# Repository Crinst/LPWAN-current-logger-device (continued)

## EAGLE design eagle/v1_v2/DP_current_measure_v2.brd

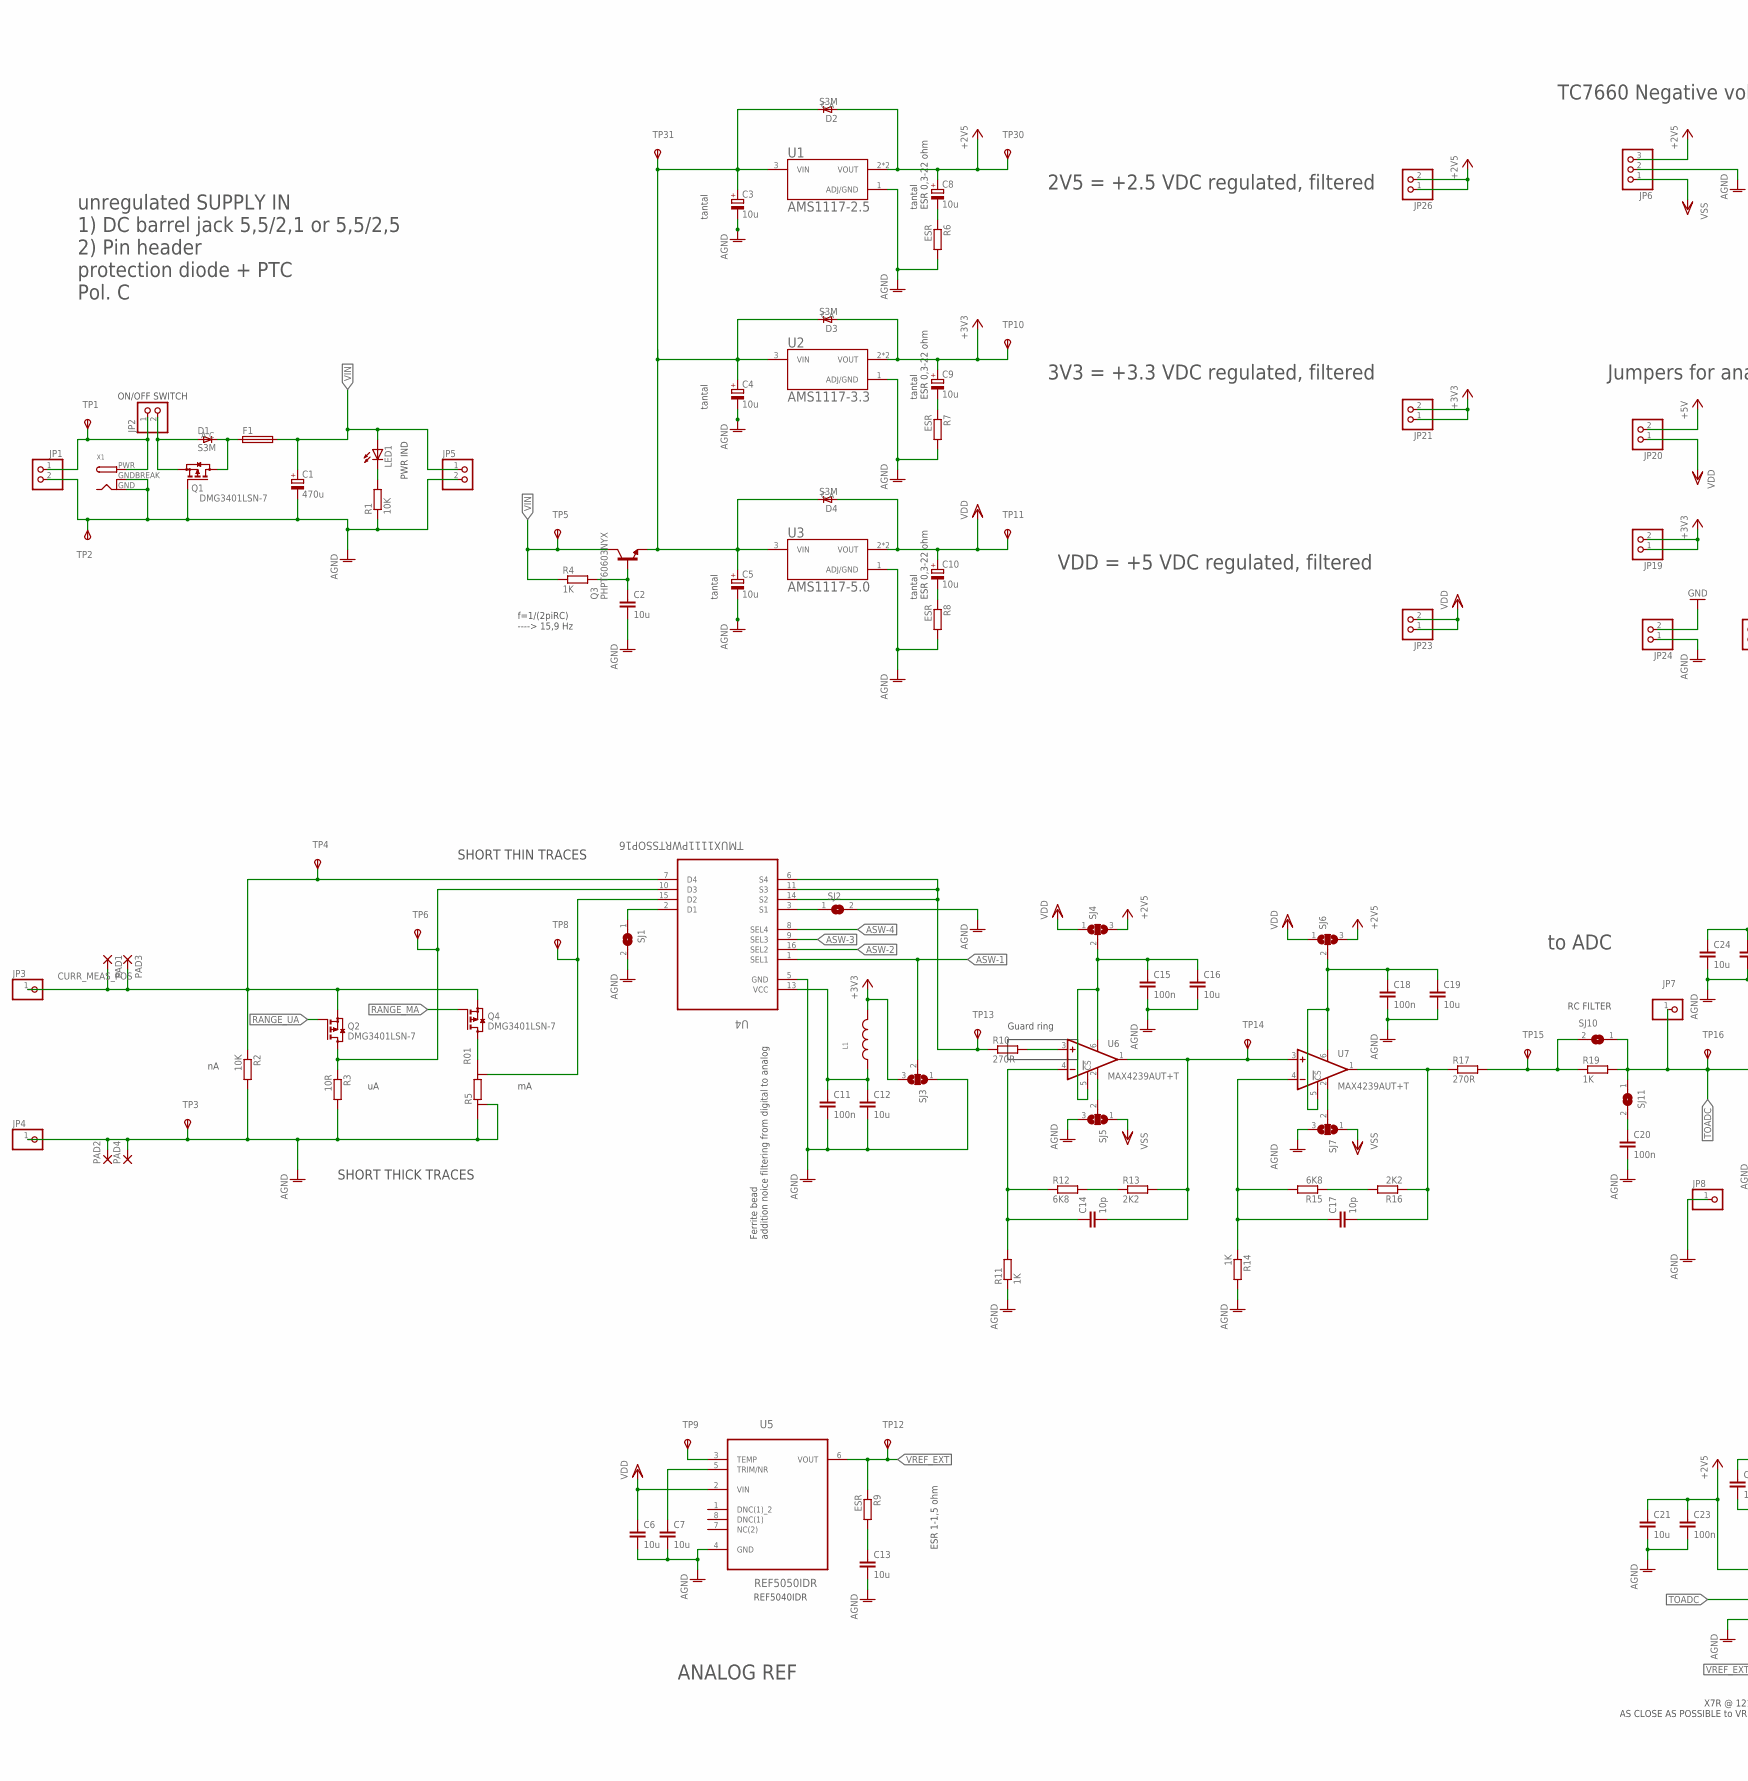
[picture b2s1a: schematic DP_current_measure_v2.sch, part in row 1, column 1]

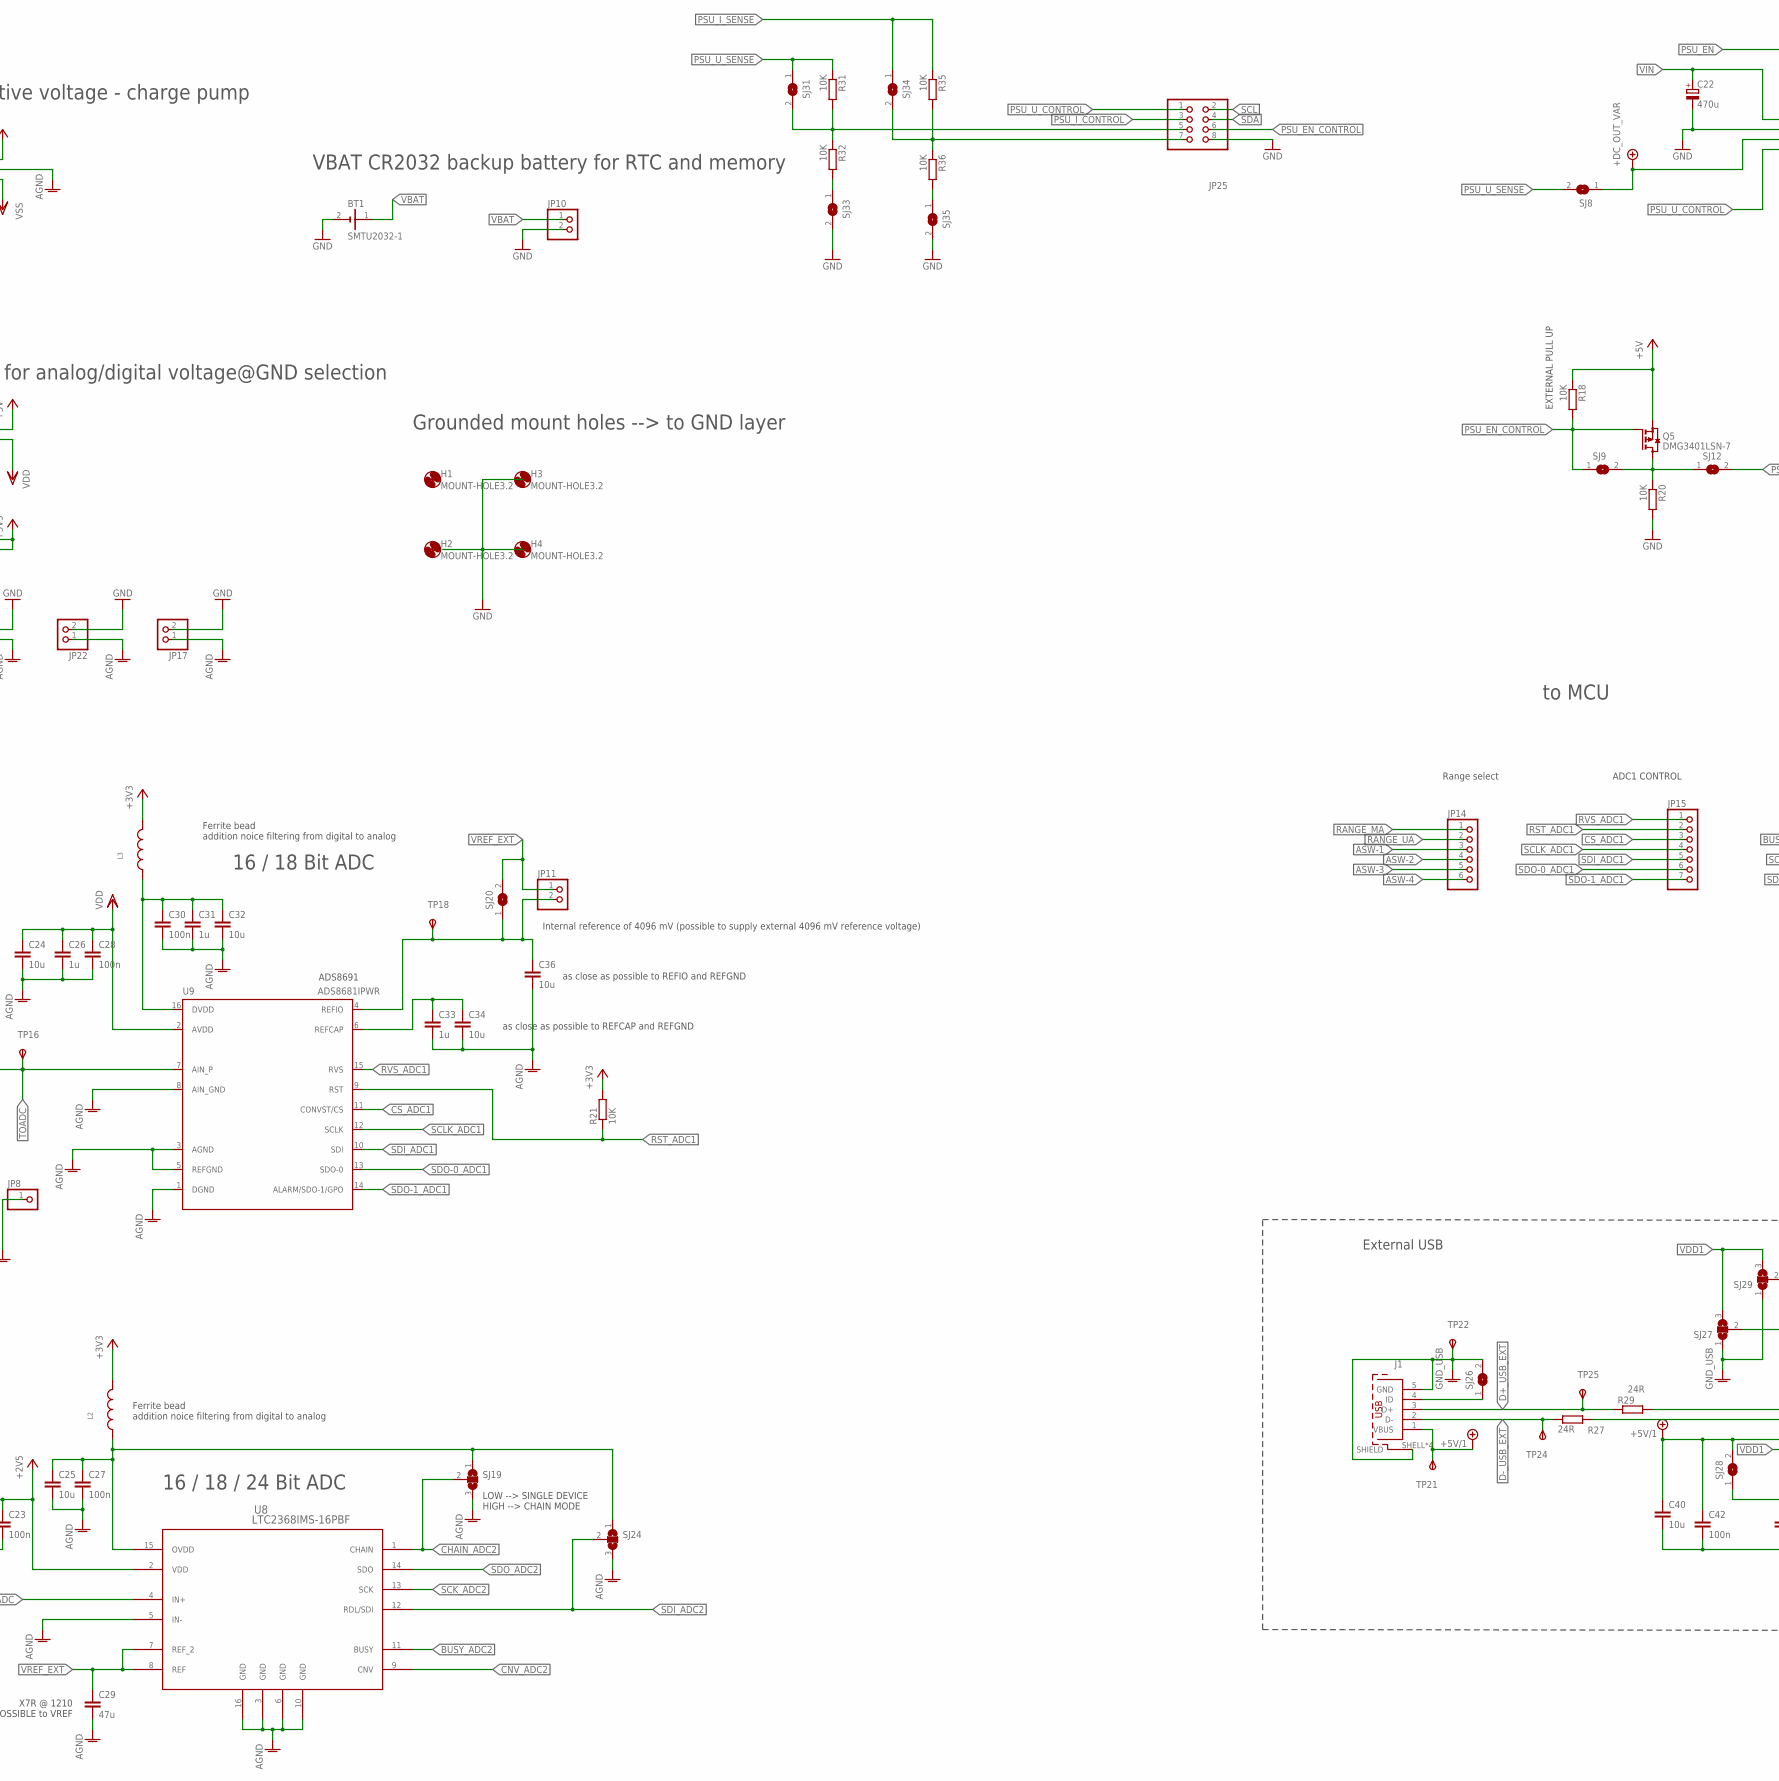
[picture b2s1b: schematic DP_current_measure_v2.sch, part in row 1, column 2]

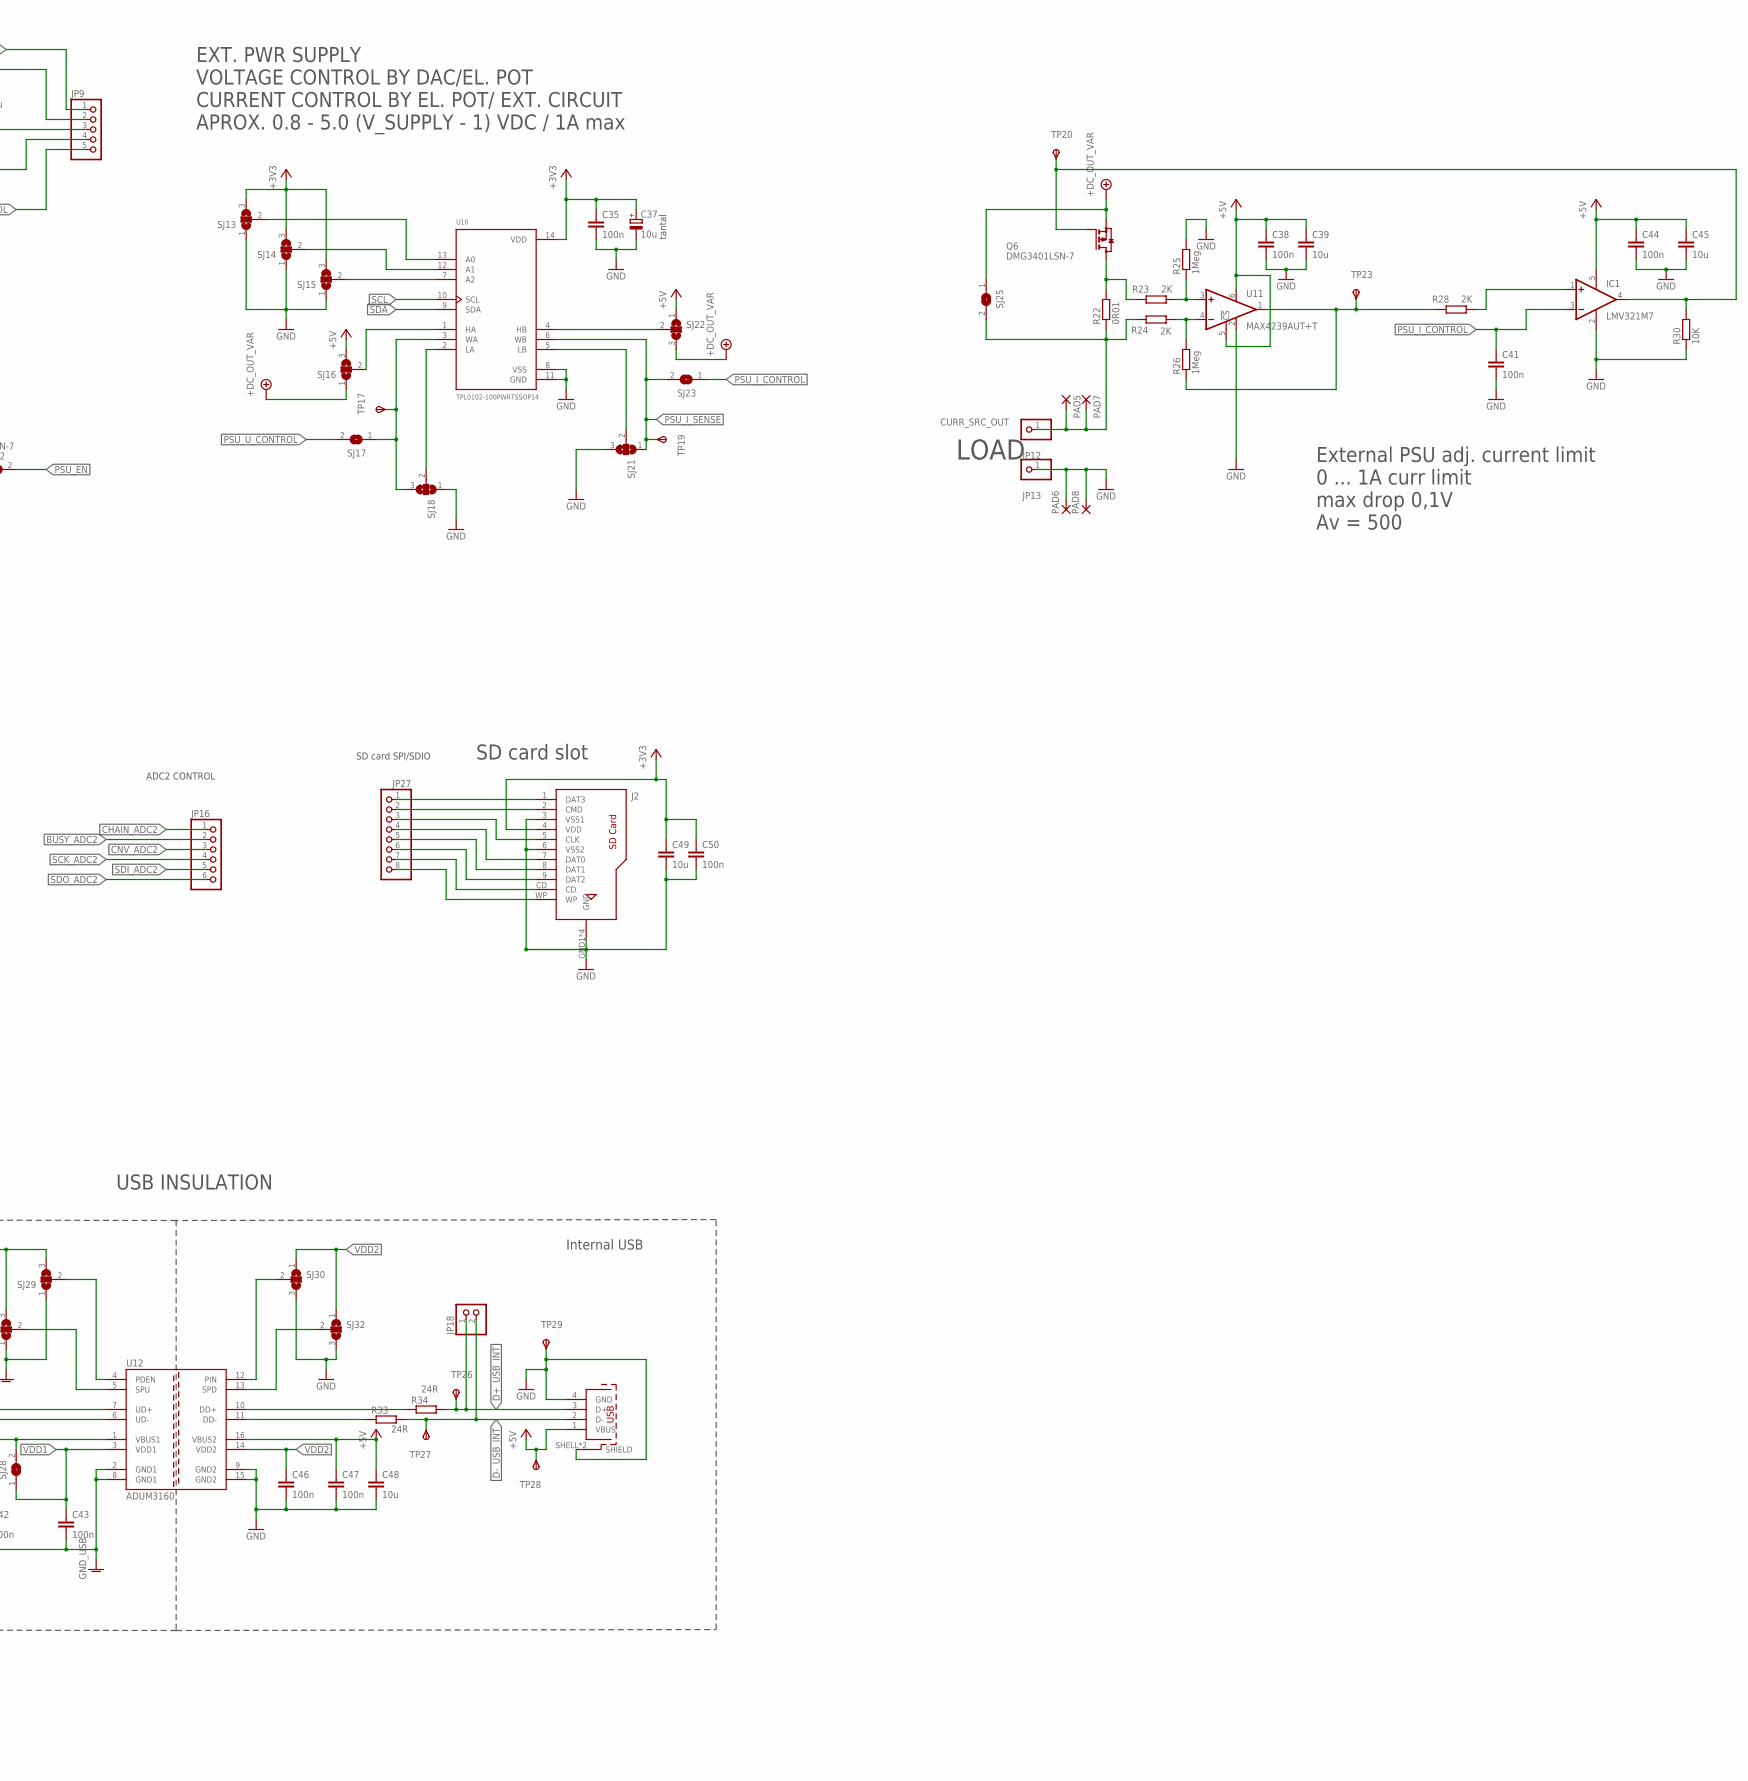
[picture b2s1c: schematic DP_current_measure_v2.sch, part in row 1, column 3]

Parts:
BT1: SMTU2032-1; RENATA_SMTU2032-1
C1, C22: 470u; PANASONIC_G
C2, C6, C7, C12, C13, C16, C19, C21, C24, C25, C32, C34, C36, C39, C40, C45, C48, C49: 10u; C1206
C3, C4, C5, C8, C9, C10, C37: 10u; SMC_B
C11, C15, C18, C23, C27, C28, C30, C35, C38, C41, C42, C43, C44, C46, C47, C50: 100n; C0805
C14, C17: 10p; C0805
C20: 100n; C1206
C26, C31, C33: 1u; C0805
C29: 47u; C1210
D1, D2, D3, D4: S3M; DO214AC
F1: MF-MSMF050-2; 1812
H1, H2, H3, H4: MOUNT-HOLE3.2; 3,2
IC1: LMV321M7; SC70-5L
J1: 629105150521
J2: 693063020911
J3: 614004185023
JP1, JP2, JP5, JP10, JP11, JP17, JP18, JP19, JP20, JP21, JP22, JP23, JP24, JP26: PINHD-1X2; 1X02
JP3, JP4, JP7, JP8, JP12, JP13: PINHD-1X1; 1X01
JP6: PINHD-1X3; 1X03
JP9: PSU_STEP_DOWN; 1X05
JP14, JP16: PINHD-1X6; 1X06
JP15: PINHD-1X7; 1X07
JP25: PINHD-2X4; 2X04
JP27: PINHD-1X8; 1X08
L1, L2, L3: WE-CBF_0805_742792036_WB_HS; WE-CBF_0805(W=3.0)
LED1: LEDCHIPLED_0805; CHIPLED_0805
PAD1, PAD2, PAD3, PAD4, PAD5, PAD6, PAD7, PAD8: WIREPADSMD2,54-5,08; SMD2,54-5,08
Q1, Q2, Q4, Q5, Q6: DMG3401LSN-7; SOT23
Q3: PHPT60603NYX; TO127P600X120-5N
R1, R2, R18, R20, R21, R30, R31, R32, R35, R36: 10K; R0805
R3: 10R; R0805
R4, R11, R14, R19: 1K; R0805
R5: R01; R2512
R6, R7, R8, R9: ESR; R0805
R10, R17: 270R; R0805
R12, R15: 6K8; R0805
R13, R16: 2K2; R0805
R22: 0R01; R0805
R23, R24, R28: 2K; R0805
R25, R26: 1Meg; R0805
R27, R29, R33, R34: 24R; R0805
SJ1, SJ2, SJ8, SJ9, SJ10, SJ11, SJ12, SJ17, SJ20, SJ23, SJ25, SJ26, SJ28, SJ31, SJ33, SJ34, SJ35: SJ
SJ3, SJ4, SJ5, SJ6, SJ7, SJ13, SJ14, SJ15, SJ16, SJ18, SJ19, SJ21, SJ22, SJ24, SJ27, SJ29, SJ30, SJ32: SJ2W; SJ_2
TP1, TP2, TP3, TP4, TP5, TP6, TP8, TP9, TP10, TP11, TP12, TP13, TP14, TP15, TP16, TP17, TP18, TP19, TP20, TP21, TP22, TP23, TP24, TP25, TP26, TP27, TP28, TP29, TP30, TP31: TPSB1,27; B1,27
U1: AMS1117-2.5; SOT229P700X180-4N
U2: AMS1117-3.3; SOT229P700X180-4N
U3: AMS1117-5.0; SOT229P700X180-4N
U4: TMUX1111PWRTSSOP16; SOP65P640X110-16N
U5: REF5050IDR; SOIC127P600X175-8N
U6, U7, U11: MAX4239AUT+T; SOT23-6
U8: LTC2368IMS-16PBF; MSOP-16_MS
U9: ADS8681IPWR; SOP65P640X120-16N
U10: TPL0102-100PWRTSSOP14; SOP65P640X120-14N
U12: ADUM3160; SO16W
X1: DCBARRELPTH; DCJACK_2MM_PTH

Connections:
+2V5: C8.+, C21.1, C23.1, D2.A, JP6.3, JP26.1, JP26.2, SJ4.3, SJ6.3, TP30.TP, U1.2 (VOUT), U1.4 (VOUT), U8.2 (VDD)
+3V3: C9.+, C35.1, C37.+, C49.1, C50.1, D3.A, J2.4 (VDD), JP19.1, JP19.2, JP21.1, JP21.2, L1.2, L2.2, L3.2, R21.2, SJ3.3, SJ13.3, SJ14.3, SJ15.3, TP10.TP, U2.2 (VOUT), U2.4 (VOUT), U10.14 (VDD)
+5V: C38.1, C39.1, C44.1, C45.1, C47.1, C48.1, IC1.5 (V+), J3.1 (VBUS), JP20.2, Q5.2 (S), R18.1, SJ16.3, SJ22.1, TP28.TP, U11.5 (!CS), U11.6 (V+), U12.16 (VBUS2)
+5V/1: C40.1, C42.1, J1.1 (VBUS), SJ28.2, TP21.TP, U12.1 (VBUS1)
AGND: C1.-, C2.2, C3.-, C4.-, C5.-, C6.2, C7.2, C11.2, C12.2, C13.2, C15.2, C16.2, C18.2, C19.2, C20.2, C21.2, C23.2, C24.2, C25.2, C26.2, C27.2, C28.2, C29.2, C30.2, C31.2, C32.2, C33.2, C34.2, C36.2, JP1.2, JP4.1, JP5.2, JP6.2, JP8.1, JP17.1, JP22.1, JP24.1, PAD2.1, PAD4.1, Q1.1 (G), R1.1, R2.2, R3.2, R5.E1, R5.I1, R6.2, R7.2, R8.2, R11.1, R14.2, SJ1.2, SJ2.2, SJ3.1, SJ5.3, SJ7.3, SJ19.3, SJ24.3, TP2.TP, TP3.TP, U1.1 (ADJ/GND), U2.1 (ADJ/GND), U3.1 (ADJ/GND), U4.5 (GND), U5.4 (GND), U8.3 (GND), U8.5 (IN-), U8.6 (GND), U8.10 (GND), U8.16 (GND), U9.1 (DGND), U9.3 (AGND), U9.5 (REFGND), U9.8 (AIN_GND), X1.GND, X1.GNDBREAK
ASW-1: JP14.3, SJ3.2, U4.1 (SEL1)
ASW-2: JP14.4, U4.16 (SEL2)
ASW-3: JP14.5, U4.9 (SEL3)
ASW-4: JP14.6, U4.8 (SEL4)
BUSY_ADC2: JP16.2, U8.11 (BUSY)
CHAIN_ADC2: JP16.1, SJ19.2, U8.1 (CHAIN)
CNV_ADC2: JP16.3, U8.9 (CNV)
CS_ADC1: JP15.3, U9.11 (CONVST/CS)
CURR_MEAS_POS: JP3.1, PAD1.1, PAD3.1, Q2.2 (S), Q4.2 (S), R2.1, TP4.TP, U4.7 (D4)
CURR_SRC_OUT: JP12.1, PAD5.1, PAD7.1, R22.1, R24.1, SJ25.2
D+_USB_EXT: J1.3 (D+), R29.1, TP25.TP
D+_USB_INT: J3.3 (D+), JP18.1, R34.2, TP26.TP
D-_USB_EXT: J1.2 (D-), R27.1, TP24.TP
D-_USB_INT: J3.2 (D-), JP18.2, R33.2, TP27.TP
DC_OUT_VAR: JP9.4, Q6.2 (S), SJ8.1, SJ16.1, SJ22.3, SJ25.1
GND: BT1.2 (-), C22.-, C35.2, C37.-, C38.2, C39.2, C41.2, C44.2, C45.2, C46.2, C47.2, C48.2, C49.2, C50.2, IC1.2 (V-), J2.3 (VSS1), J2.6 (VSS2), J2.GND1 (GND), J2.GND2 (GND), J2.GND3 (GND), J2.GND4 (GND), J3.4 (GND), J3.SHELL (SHIELD), J3.SHELL1 (SHIELD), JP9.3, JP10.2, JP13.1, JP17.2, JP22.2, JP24.2, JP25.8, PAD6.1, PAD8.1, R20.2, R25.2, R30.1, SJ13.1, SJ14.1, SJ15.1, SJ18.1, SJ21.3, SJ30.3, SJ32.3, SJ33.2, SJ35.2, TP29.TP, U10.8 (VSS), U10.11 (GND), U11.2 (V-), U12.9 (GND2), U12.15 (GND2)
GND_EXT: C40.2, C42.2, C43.2, J1.5 (GND), J1.SHELL (SHIELD), J1.SHELL1 (SHIELD), J1.SHELL2 (SHIELD), J1.SHELL3 (SHIELD), SJ26.2, SJ27.1, SJ29.1, TP22.TP, U12.2 (GND1), U12.8 (GND1)
MA_RANGE_SENSE: R5.E2, TP8.TP, U4.15 (D2)
unnamed: C17.2, R16.1, R17.1, U7.1 (OUT)
unnamed: R15.1, R16.2
unnamed: C17.1, R14.1, R15.2, U7.4 (-IN)
unnamed: R12.2, R13.1
unnamed: C14.2, R13.2, TP14.TP, U6.1 (OUT), U7.3 (+IN)
unnamed: R10.1, TP13.TP, U4.6 (S4), U4.11 (S3), U4.14 (S2)
unnamed: C14.1, R11.2, R12.1, U6.4 (-IN)
unnamed: C11.1, C12.1, L1.1, U4.13 (VCC)
unnamed: SJ16.2, U10.1 (HA)
unnamed: SJ17.1, SJ18.3, TP17.TP, U10.3 (WA)
unnamed: Q6.3 (D), R22.2, R23.1
unnamed: SJ15.2, U10.7 (A2)
unnamed: SJ7.2, U7.2 (V-)
unnamed: R10.2, U6.3 (+IN)
unnamed: C9.-, R7.1
unnamed: Q4.3 (D), R5.I2
unnamed: SJ5.2, U6.2 (V-)
unnamed: R17.2, R19.1, SJ10.2, TP15.TP
unnamed: C10.-, R8.1
unnamed: SJ13.2, U10.13 (A0)
unnamed: C8.-, R6.1
unnamed: C2.1, Q3.4 (B), R4.2
unnamed: C7.1, U5.5 (TRIM/NR)
unnamed: C20.1, SJ11.2
unnamed: SJ14.2, U10.12 (A1)
unnamed: JP25.7, R35.2, R36.1, SJ34.2
unnamed: JP25.5, R31.2, R32.1, SJ31.2
unnamed: R36.2, SJ35.1
unnamed: R32.2, SJ33.1
unnamed: R26.1, R28.1, TP23.TP, U11.1 (OUT)
unnamed: SJ22.2, U10.4 (HB)
unnamed: J1.4 (ID), SJ26.1
unnamed: R23.2, R25.1, U11.3 (+IN)
unnamed: SJ18.2, U10.2 (LA)
unnamed: IC1.4 (OUT), Q6.1 (G), R30.2, TP20.TP
unnamed: R24.2, R26.2, U11.4 (-IN)
unnamed: C18.1, C19.1, SJ6.2, U7.5 (!CS), U7.6 (V+)
unnamed: D1.C, F1.1, Q1.3 (D)
unnamed: C33.1, C34.1, U9.6 (REFCAP)
unnamed: C36.1, JP11.2, SJ20.1, TP18.TP, U9.4 (REFIO)
unnamed: D1.A, JP2.2, Q1.2 (S)
unnamed: R34.1, U12.10 (DD+)
unnamed: LED1.C, R1.2
unnamed: SJ21.2, U10.5 (LB)
unnamed: C15.1, C16.1, SJ4.2, U6.5 (!CS), U6.6 (V+)
unnamed: TP9.TP, U5.3 (TEMP)
unnamed: J2.1 (DAT3), JP27.1
unnamed: J2.2 (CMD), JP27.2
unnamed: J2.5 (CLK), JP27.3
unnamed: J2.7 (DAT0), JP27.4
unnamed: SJ30.2, U12.12 (PIN)
unnamed: SJ32.2, U12.13 (SPD)
unnamed: SJ27.2, U12.5 (SPU)
unnamed: SJ29.2, U12.4 (PDEN)
unnamed: SJ2.1, U4.3 (S1)
unnamed: SJ1.1, U4.2 (D1)
unnamed: J2.8 (DAT1), JP27.5
unnamed: C13.1, R9.2
unnamed: J2.9 (DAT2), JP27.6
unnamed: J2.CD, JP27.7
unnamed: J2.WP, JP27.8
unnamed: JP1.1, JP2.1, TP1.TP, X1.PWR
unnamed: C30.1, C31.1, C32.1, L3.1, U9.16 (DVDD)
unnamed: C25.1, C27.1, L2.1, SJ19.1, SJ24.1, U8.15 (OVDD)
OPAMP_LEADS: IC1.1 (+IN), R28.2
PSU_EN: JP9.1, SJ12.2
PSU_EN_CONTROL: JP25.6, Q5.1 (G), R18.2, SJ9.1
PSU_EN_LEAD: Q5.3 (D), R20.1, SJ9.2, SJ12.1
PSU_I_CONTROL: C41.1, IC1.3 (-IN), JP25.3, SJ23.1
PSU_I_SENSE: R35.1, SJ21.1, SJ23.2, SJ34.1, TP19.TP, U10.6 (WB)
PSU_U_CONTROL: JP9.5, JP25.1, SJ17.2
PSU_U_SENSE: R31.1, SJ8.2, SJ31.1
RANGE_MA: JP14.1, Q4.1 (G)
RANGE_UA: JP14.2, Q2.1 (G)
RST_ADC1: JP15.2, R21.1, U9.9 (RST)
RVS_ADC1: JP15.1, U9.15 (RVS)
SCK_ADC2: JP16.4, U8.13 (SCK)
SCL: JP25.2, U10.10 (SCL)
SCLK_ADC1: JP15.4, U9.12 (SCLK)
SDA: JP25.4, U10.9 (SDA)
SDI_ADC1: JP15.5, U9.10 (SDI)
SDI_ADC2: JP16.5, SJ24.2, U8.12 (RDL/SDI)
SDO-0_ADC1: JP15.6, U9.13 (SDO-0)
SDO-1_ADC1: JP15.7, U9.14 (ALARM/SDO-1/GPO)
SDO_ADC2: JP16.6, U8.14 (SDO)
TOADC: JP7.1, R19.2, SJ10.1, SJ11.1, TP16.TP, U8.4 (IN+), U9.7 (AIN_P)
UA_RANGE_SENSE: Q2.3 (D), R3.1, TP6.TP, U4.10 (D3)
USB_EXT_N: R27.2, U12.6 (UD-)
USB_EXT_P: R29.2, U12.7 (UD+)
USB_INT_N: R33.1, U12.11 (DD-)
VBAT: BT1.1 (+), JP10.1
VDD: C6.1, C10.+, C24.1, C26.1, C28.1, D4.A, JP20.1, JP23.1, JP23.2, SJ4.1, SJ6.1, TP11.TP, U3.2 (VOUT), U3.4 (VOUT), U5.2 (VIN), U9.2 (AVDD)
VDD1: C43.1, SJ27.3, SJ28.1, SJ29.3, U12.3 (VDD1)
VDD2: C46.1, SJ30.1, SJ32.1, U12.14 (VDD2)
VIN: C1.+, C22.+, F1.2, JP5.1, JP9.2, LED1.A, Q3.5 (C), R4.1, TP5.TP
VREF_EXT: C29.1, JP11.1, R9.1, SJ20.2, TP12.TP, U5.6 (VOUT), U8.7 (REF_2), U8.8 (REF)
VSS: JP6.1, SJ5.1, SJ7.1
V_FILTR_UNREG: C3.+, C4.+, C5.+, D2.C, D3.C, D4.C, Q3.1 (E), Q3.2 (E), Q3.3 (E), TP31.TP, U1.3 (VIN), U2.3 (VIN), U3.3 (VIN)

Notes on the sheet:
SHORT THICK TRACES
SHORT THIN TRACES
unregulated SUPPLY IN 1) DC barrel jack 5,5/2,1 or 5,5/2,5 2) Pin header protection diode + PTC Pol. C
to MCU
to ADC
tantal
tantal ESR 0,3-22 ohm
f=1/(2piRC) ----> 15,9 Hz
VDD = +5 VDC regulated, filtered
as close as possible to REFIO and REFGND
as close as possible to REFCAP and REFGND
ADS8691
3V3 = +3.3 VDC regulated, filtered
REF5040IDR
LOW --> SINGLE DEVICE HIGH --> CHAIN MODE
X7R @ 1210 AS CLOSE AS POSSIBLE to VREF
16 / 18 / 24 Bit ADC
16 / 18 Bit ADC
Internal reference of 4096 mV (possible to supply external 4096 mV reference voltage)
RC FILTER
ADC2 CONTROL
ADC1 CONTROL
EXT. PWR SUPPLY VOLTAGE CONTROL BY DAC/EL. POT CURRENT CONTROL BY EL. POT/ EXT. CIRCUIT APROX. 0.8 - 5.0 (V_SUPPLY - 1) VDC / 1A max
ANALOG REF
EXTERNAL PULL UP
LOAD
External PSU adj. current limit 0 ... 1A curr limit max drop 0,1V Av = 500
USB INSULATION
PWR IND
TC7660 Negative voltage - charge pump
VBAT CR2032 backup battery for RTC and memory
Guard ring
SD card slot
SD card SPI/SDIO
Range select
ESR 1-1,5 ohm
ON/OFF SWITCH
2V5 = +2.5 VDC regulated, filtered
External USB
Internal USB

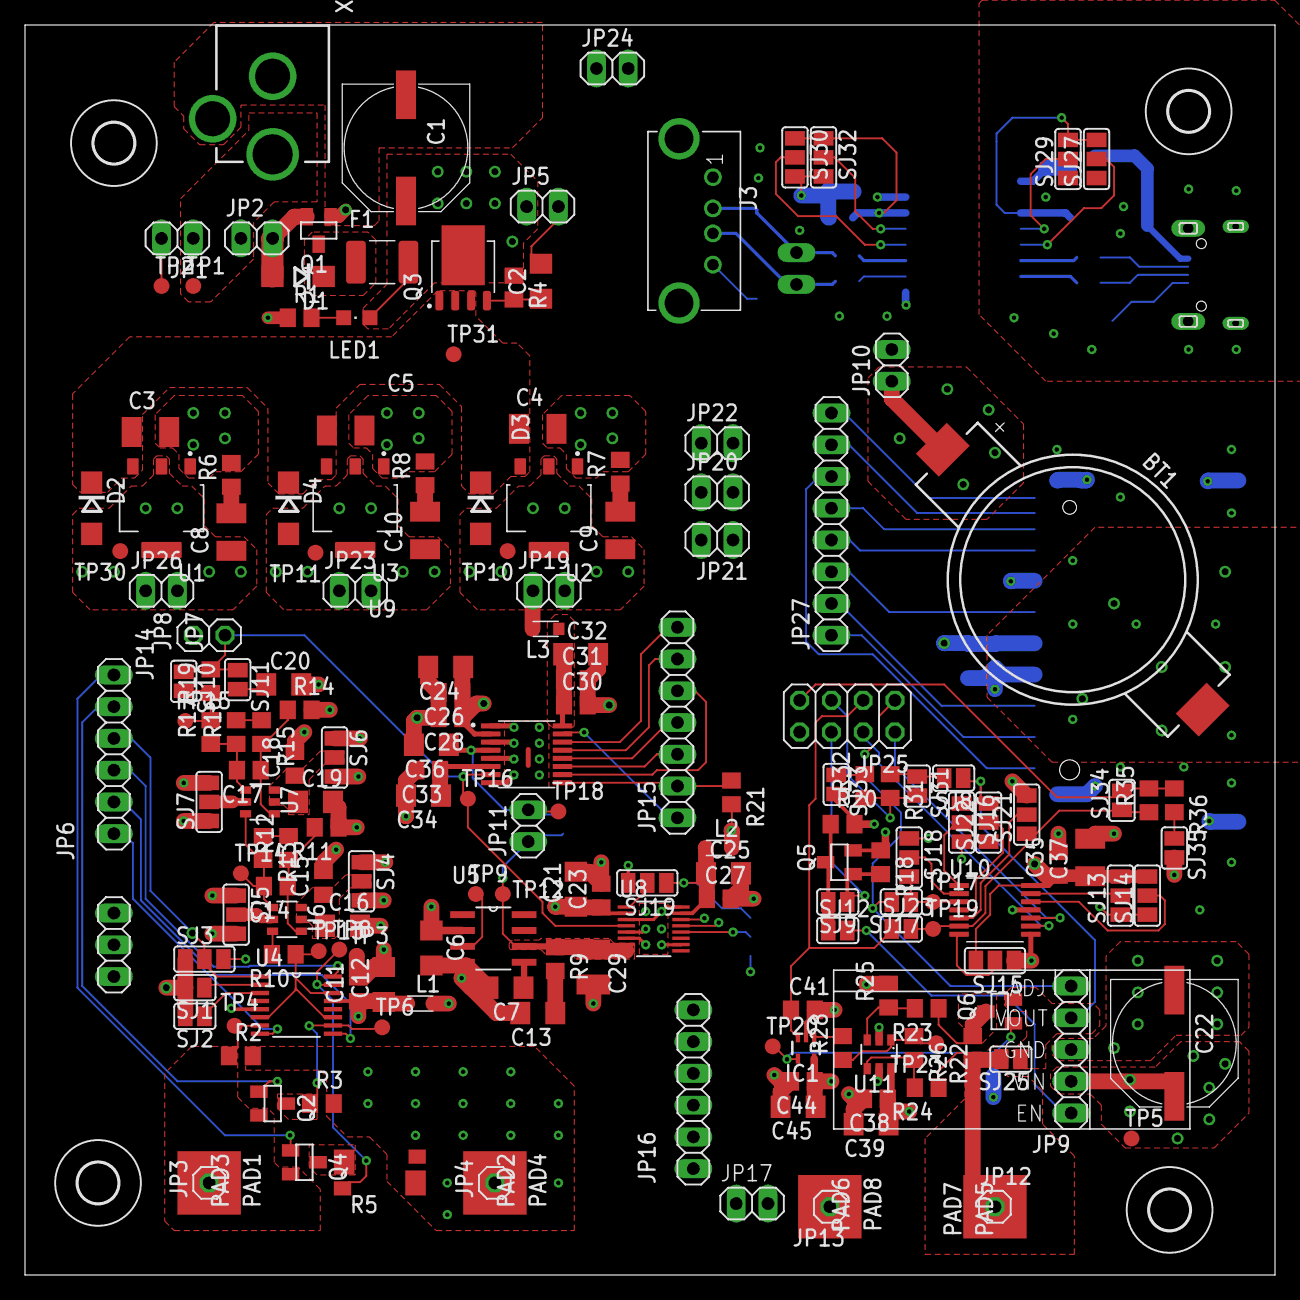
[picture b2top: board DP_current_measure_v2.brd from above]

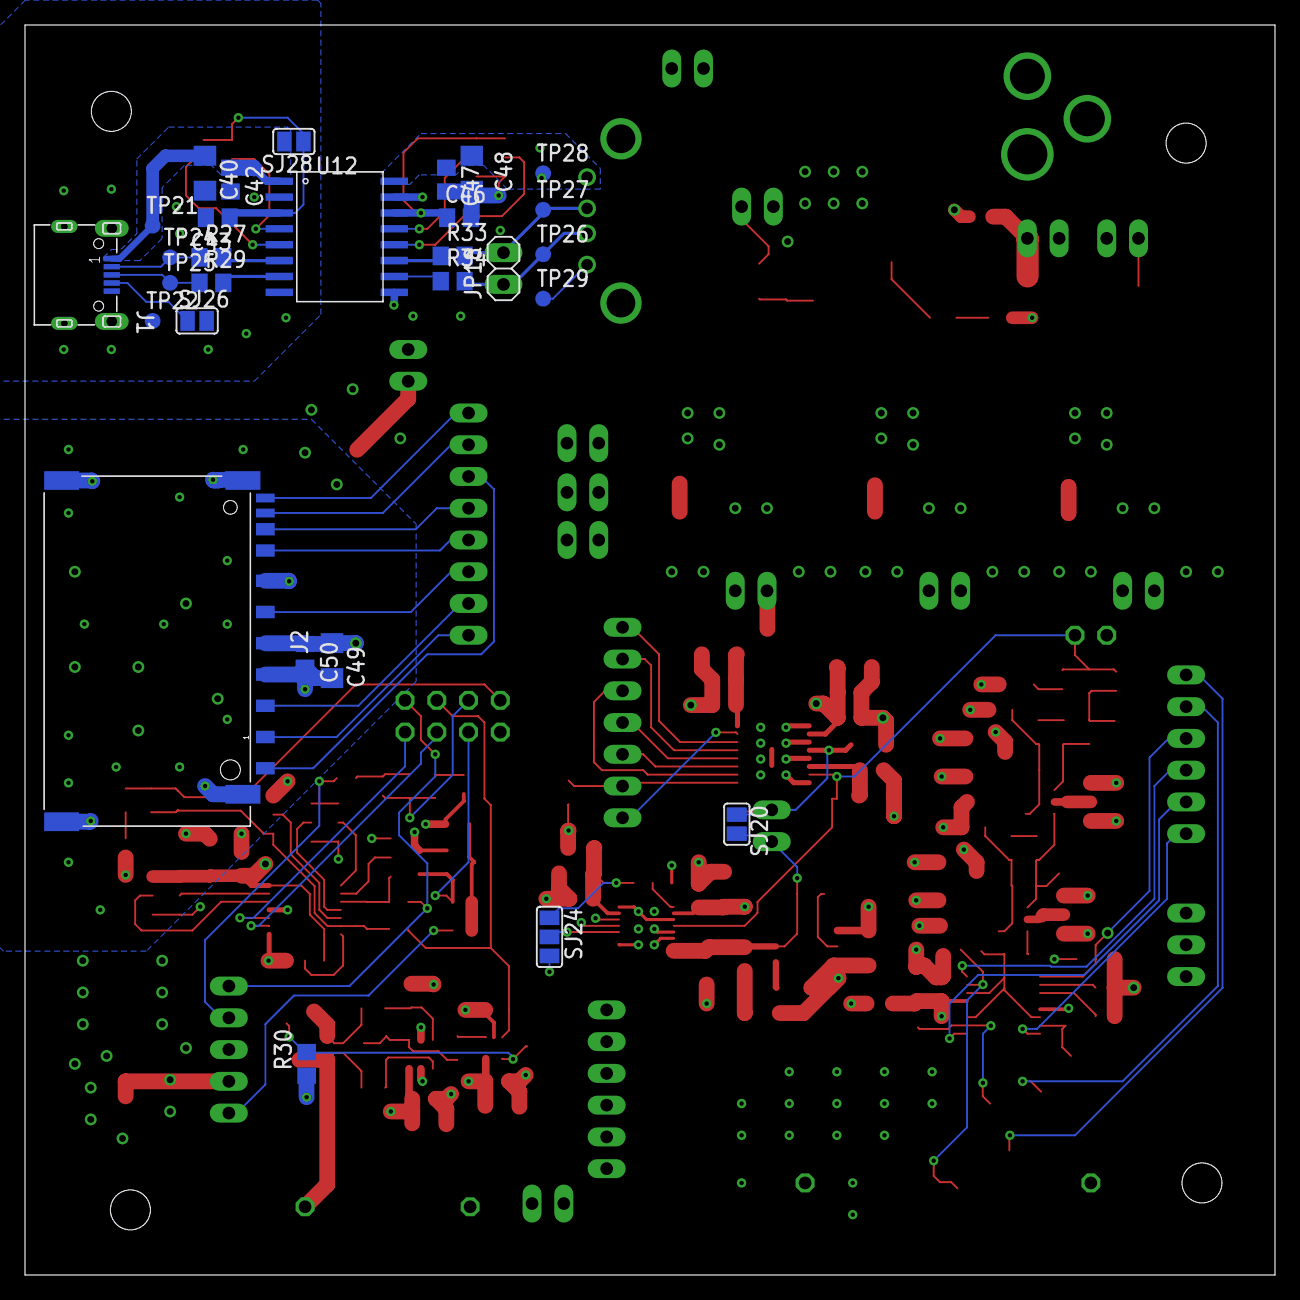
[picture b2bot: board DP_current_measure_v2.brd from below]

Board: 4 copper layers, 99.9 x 99.9 mm, 223 parts (29 on the bottom side), 121 nets.

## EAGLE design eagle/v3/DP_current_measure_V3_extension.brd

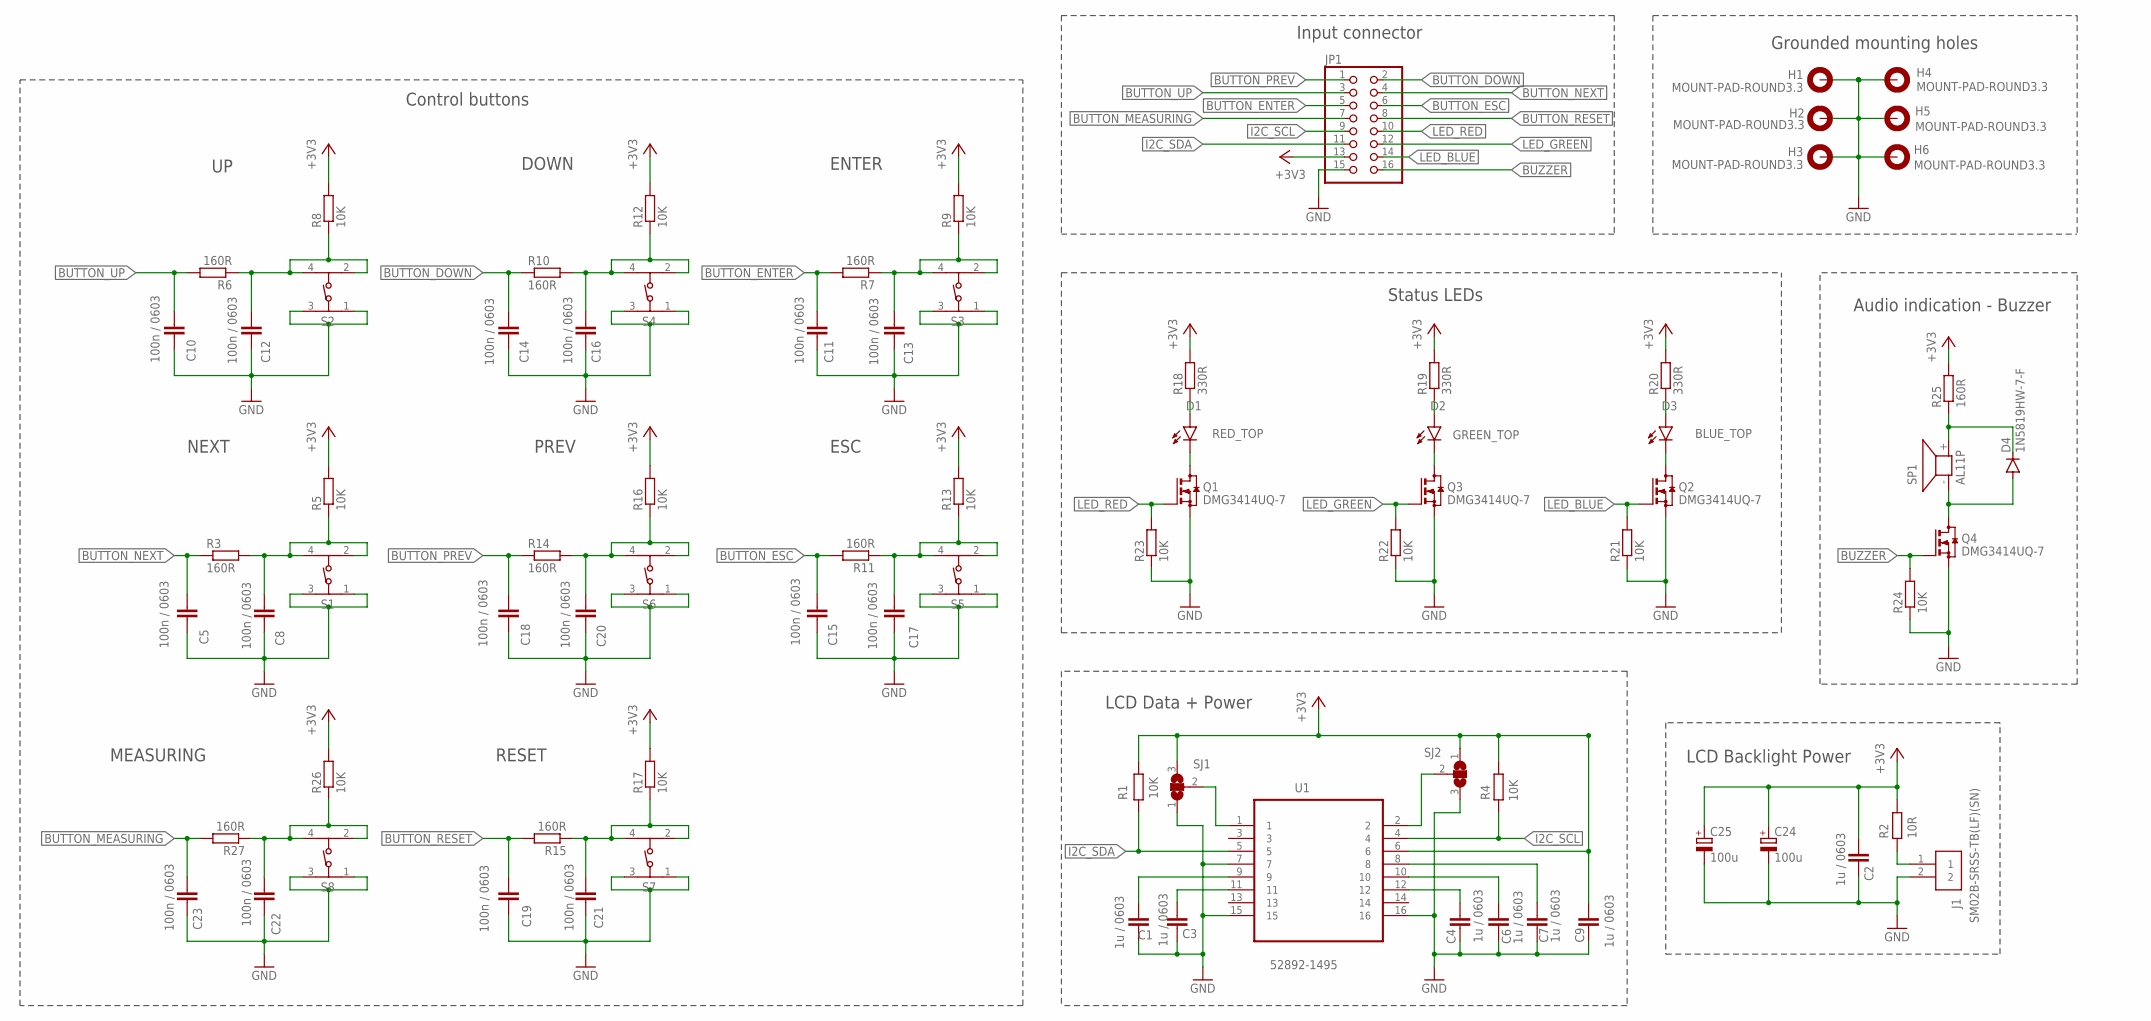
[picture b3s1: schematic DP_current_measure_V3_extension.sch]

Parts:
C1, C2, C3, C4, C6, C7, C9: 1u / 0603; C0603
C5, C8, C10, C11, C12, C13, C14, C15, C16, C17, C18, C19, C20, C21, C22, C23: 100n / 0603; C0603
C24, C25: 100u; SMC_B
D1: RED_TOP; LED-0603
D2: GREEN_TOP; LED-0603
D3: BLUE_TOP; LED-0603
D4: 1N5819HW-7-F; SOD-123_MINI-SMA
H1, H2, H3, H4, H5, H6: MOUNT-PAD-ROUND3.3; 3,3-PAD
J1: SM02B-SRSS-TB(LF)(SN)
JP1: PINHD-2X8; 2X08
Q1, Q2, Q3, Q4: DMG3414UQ-7; SOT23
R1, R4, R5, R8, R9, R12, R13, R16, R17, R21, R22, R23, R24, R26: 10K; R0603
R2: 10R; R0603
R3, R6, R7, R10, R11, R14, R15, R25, R27: 160R; R0603
R18, R19, R20: 330R; R0603
S1, S2, S3, S4, S5, S6, S7, S8: 430152095826
SJ1, SJ2: SJ2W; SJ_2
SP1: AL11P
U1: 52892-1495; MOLEX_52892-1495

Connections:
+3V3: C2.1, C9.1, C24.+, C25.+, JP1.13, R1.2, R2.2, R4.2, R5.2, R8.2, R9.2, R12.2, R13.2, R16.2, R17.2, R18.2, R19.2, R20.2, R25.2, R26.2, SJ1.3, SJ2.1, U1.6
BUTTON_DOWN: C14.1, JP1.2, R10.1
BUTTON_ENTER: C11.1, JP1.5, R7.2
BUTTON_ESC: C15.1, JP1.6, R11.2
BUTTON_MEASURING: C23.1, JP1.7, R27.2
BUTTON_NEXT: C5.1, JP1.4, R3.1
BUTTON_PREV: C18.1, JP1.1, R14.1
BUTTON_RESET: C19.1, JP1.8, R15.2
BUTTON_UP: C10.1, JP1.3, R6.2
BUZZER: JP1.16, Q4.1 (G), R24.2
GND: C1.2, C2.2, C3.2, C4.2, C5.2, C6.2, C7.2, C8.2, C9.2, C10.2, C11.2, C12.2, C13.2, C14.2, C15.2, C16.2, C17.2, C18.2, C19.2, C20.2, C21.2, C22.2, C23.2, C24.-, C25.-, H1.B3,3, H2.B3,3, H3.B3,3, H4.B3,3, H5.B3,3, H6.B3,3, J1.2, JP1.15, Q1.2 (S), Q2.2 (S), Q3.2 (S), Q4.2 (S), R21.1, R22.1, R23.1, R24.1, S1.1, S1.3, S2.1, S2.3, S3.1, S3.3, S4.1, S4.3, S5.1, S5.3, S6.1, S6.3, S7.1, S7.3, S8.1, S8.3, SJ1.1, SJ2.3, U1.7, U1.15, U1.16
I2C_SCL: JP1.9, R4.1, U1.4
I2C_SDA: JP1.11, R1.1, U1.5
LED_BLUE: JP1.14, Q2.1 (G), R21.2
LED_GREEN: JP1.12, Q3.1 (G), R22.2
LED_RED: JP1.10, Q1.1 (G), R23.2
unnamed: SJ1.2, U1.1
unnamed: J1.1, R2.1
unnamed: C12.1, R6.1, R8.1, S2.2, S2.4
unnamed: C22.1, R26.1, R27.1, S8.2, S8.4
unnamed: C1.1, U1.9
unnamed: C3.1, U1.11
unnamed: C16.1, R10.2, R12.1, S4.2, S4.4
unnamed: D1.C, Q1.3 (D)
unnamed: SJ2.2, U1.2
unnamed: C13.1, R7.1, R9.1, S3.2, S3.4
unnamed: D1.A, R18.1
unnamed: C7.1, U1.8
unnamed: C6.1, U1.10
unnamed: C4.1, U1.12
unnamed: D2.C, Q3.3 (D)
unnamed: D2.A, R19.1
unnamed: D4.A, Q4.3 (D), SP1.- (1)
unnamed: D4.C, R25.1, SP1.+ (2)
unnamed: C20.1, R14.2, R16.1, S6.2, S6.4
unnamed: C17.1, R11.1, R13.1, S5.2, S5.4
unnamed: C21.1, R15.1, R17.1, S7.2, S7.4
unnamed: D3.C, Q2.3 (D)
unnamed: D3.A, R20.1
unnamed: C8.1, R3.2, R5.1, S1.2, S1.4

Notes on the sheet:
DOWN
PREV
NEXT
ENTER
ESC
RESET
MEASURING
LCD Backlight Power
LCD Data + Power
Control buttons
Audio indication - Buzzer
Status LEDs
Input connector
Grounded mounting holes
